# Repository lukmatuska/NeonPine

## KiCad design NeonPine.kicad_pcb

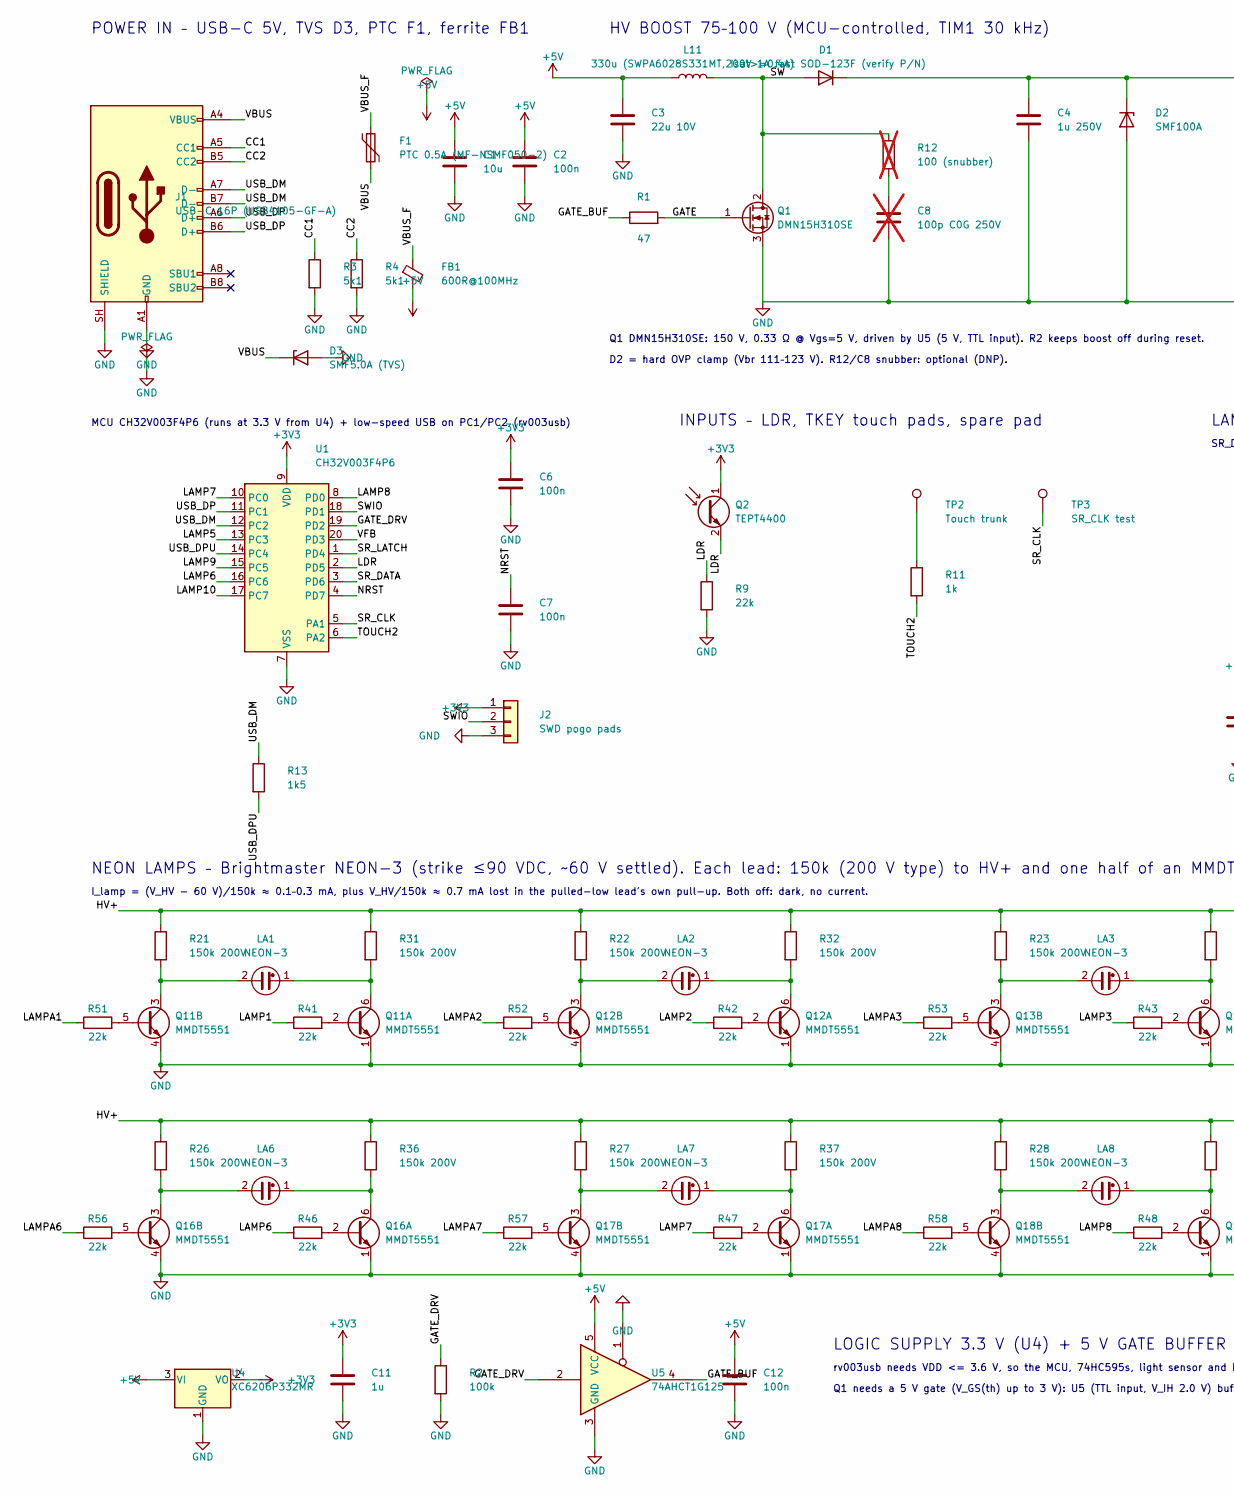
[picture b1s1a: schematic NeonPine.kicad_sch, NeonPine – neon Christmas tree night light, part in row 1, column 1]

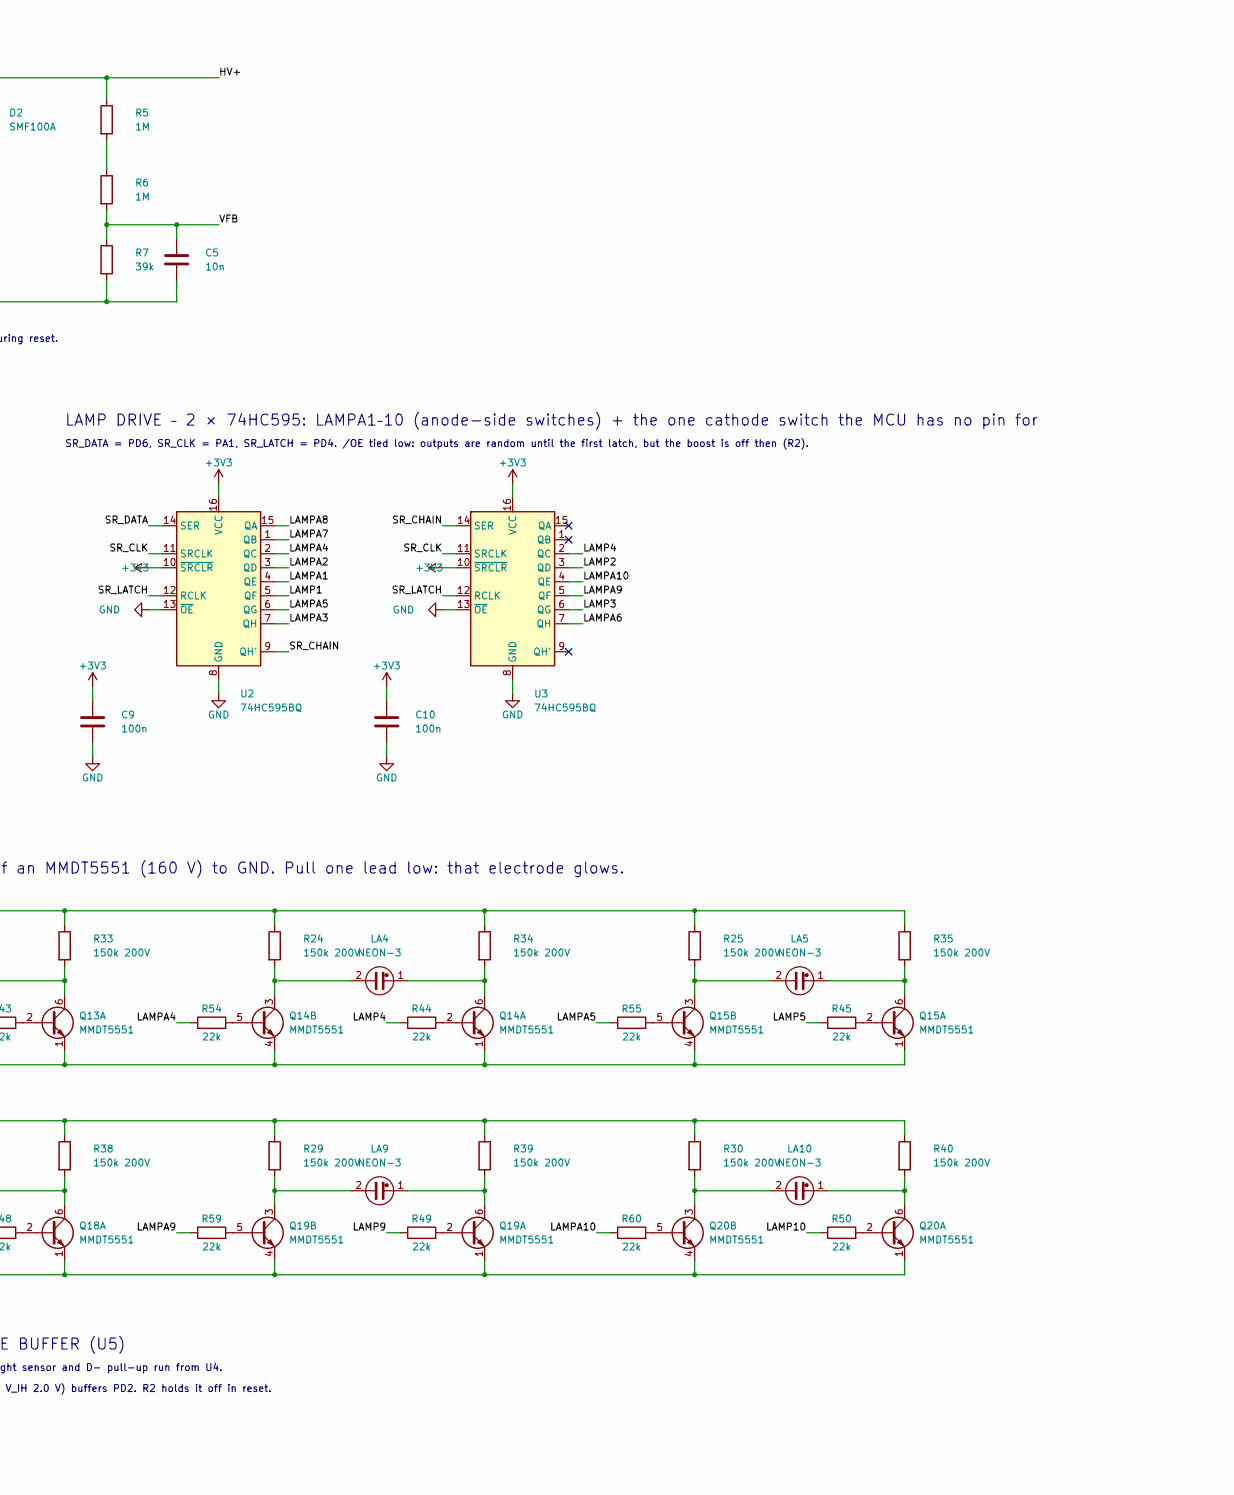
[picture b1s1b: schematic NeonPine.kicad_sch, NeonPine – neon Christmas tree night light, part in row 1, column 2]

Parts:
C1: 10u; C_0603_1608Metric
C2, C6, C7, C9, C10, C12: 100n; C_0402_1005Metric
C3: 22u 10V; C_0805_2012Metric
C4: 1u 250V; C_1210_3225Metric
C5: 10n; C_0402_1005Metric
C8: 100p C0G 250V; C_0805_2012Metric; not fitted
C11: 1u; C_0402_1005Metric
D1: 200V 1A fast SOD-123F (verify P/N); D_SOD-123F
D2: SMF100A; D_SOD-123F
D3: SMF5.0A (TVS); D_SOD-123F
F1: PTC 0.5A (MF-NSMF050-2); Fuse_1206_3216Metric
FB1: 600R@100MHz; L_0603_1608Metric
J1: USB-C 16P (USB4105-GF-A); USB_C_Receptacle_GCT_USB4105-xx-A_16P_TopMnt_Horizontal
J2: SWD pogo pads; Pogo_1x03_P2.54mm
L11: 330u (SWPA6028S331MT, Isat>=0.4A); L_6.3x6.3_H3
LA1, LA2, LA3, LA4, LA5, LA6, LA7, LA8, LA9, LA10: NEON-3; Lamp_Neon_Brightmaster_NEON-3_D4x10_P3.0
Q1: DMN15H310SE; SOT-223-3_TabPin2
Q2: TEPT4400; LED_D3.0mm
Q11, Q12, Q13, Q14, Q15, Q16, Q17, Q18, Q19, Q20: MMDT5551; SOT-363_SC-70-6
R1: 47; R_0402_1005Metric
R2: 100k; R_0402_1005Metric
R3, R4: 5k1; R_0402_1005Metric
R5, R6: 1M; R_0603_1608Metric
R7: 39k; R_0402_1005Metric
R9, R41, R42, R43, R44, R45, R46, R47, R48, R49, R50, R51, R52, R53, R54, R55, R56, R57, R58, R59, R60: 22k; R_0402_1005Metric
R11: 1k; R_0402_1005Metric
R12: 100 (snubber); R_0805_2012Metric; not fitted
R13: 1k5; R_0402_1005Metric
R21, R22, R23, R24, R25, R26, R27, R28, R29, R30, R31, R32, R33, R34, R35, R36, R37, R38, R39, R40: 150k 200V; R_0603_1608Metric
TP2: Touch trunk; TouchPad_D4.0mm_Masked
TP3: SR_CLK test; TestPoint_Pad_1.5x1.5mm
U1: CH32V003F4P6; TSSOP-20_4.4x6.5mm_P0.65mm
U2, U3: 74HC595BQ; DHVQFN-16-1EP_2.5x3.5mm_P0.5mm_EP1x2mm_EPGND
U4: XC6206P332MR; SOT-23
U5: 74AHCT1G125; SOT-353_SC-70-5

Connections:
+3V3: C6.1, C9.1, C10.1, C11.1, J2.1, Q2.1 (C), U1.9 (VDD), U2.10 (~SRCLR), U2.16 (VCC), U3.10 (~SRCLR), U3.16 (VCC), U4.2 (VO)
+5V: C1.1, C2.1, C3.1, C12.1, FB1.2, L11.1, U4.3 (VI), U5.5 (VCC)
/CC1: J1.A5 (CC1), R3.1
/CC2: J1.B5 (CC2), R4.1
/GATE: Q1.1 (G), R1.2
/GATE_BUF: R1.1, U5.4
/GATE_DRV: R2.1, U1.19 (PD2), U5.2
/HV+: C4.1, D1.1 (K), D2.1 (K), R5.1, R21.1, R22.1, R23.1, R24.1, R25.1, R26.1, R27.1, R28.1, R29.1, R30.1, R31.1, R32.1, R33.1, R34.1, R35.1, R36.1, R37.1, R38.1, R39.1, R40.1
/LAMP1: R41.1, U2.5 (QF)
/LAMP2: R42.1, U3.3 (QD)
/LAMP3: R43.1, U3.6 (QG)
/LAMP4: R44.1, U3.2 (QC)
/LAMP5: R45.1, U1.13 (PC3)
/LAMP6: R46.1, U1.16 (PC6)
/LAMP7: R47.1, U1.10 (PC0)
/LAMP8: R48.1, U1.8 (PD0)
/LAMP9: R49.1, U1.15 (PC5)
/LAMP10: R50.1, U1.17 (PC7)
/LAMPA1: R51.1, U2.4 (QE)
/LAMPA2: R52.1, U2.3 (QD)
/LAMPA3: R53.1, U2.7 (QH)
/LAMPA4: R54.1, U2.2 (QC)
/LAMPA5: R55.1, U2.6 (QG)
/LAMPA6: R56.1, U3.7 (QH)
/LAMPA7: R57.1, U2.1 (QB)
/LAMPA8: R58.1, U2.15 (QA)
/LAMPA9: R59.1, U3.5 (QF)
/LAMPA10: R60.1, U3.4 (QE)
/LDR: Q2.2 (E), R9.1, U1.2 (PD5)
/NRST: C7.1, U1.4 (PD7)
/SR_CHAIN: U2.9 (QH'), U3.14 (SER)
/SR_CLK: TP3.1 (1_1), U1.5 (PA1), U2.11 (SRCLK), U3.11 (SRCLK)
/SR_DATA: U1.3 (PD6), U2.14 (SER)
/SR_LATCH: U1.1 (PD4), U2.12 (RCLK), U3.12 (RCLK)
/SW: D1.2 (A), L11.2, Q1.2 (D), R12.1
/SWIO: J2.2, U1.18 (PD1)
/TOUCH2: R11.2, U1.6 (PA2)
/USB_DM: J1.A7 (D-), J1.B7 (D-), R13.1, U1.12 (PC2)
/USB_DP: J1.A6 (D+), J1.B6 (D+), U1.11 (PC1)
/USB_DPU: R13.2, U1.14 (PC4)
/VBUS: D3.1 (K), F1.2, J1.A4 (VBUS), J1.A9 (VBUS), J1.B4 (VBUS), J1.B9 (VBUS)
/VBUS_F: F1.1, FB1.1
/VFB: C5.1, R6.2, R7.1, U1.20 (PD3)
GND: C1.2, C2.2, C3.2, C4.2, C5.2, C6.2, C7.2, C8.2, C9.2, C10.2, C11.2, C12.2, D2.2 (A), D3.2 (A), J1.A1 (GND), J1.A12 (GND), J1.B1 (GND), J1.B12 (GND), J1.SH (SHIELD), J2.3, Q1.3 (S), Q11.1 (E1), Q11.4 (E2), Q12.1 (E1), Q12.4 (E2), Q13.1 (E1), Q13.4 (E2), Q14.1 (E1), Q14.4 (E2), Q15.1 (E1), Q15.4 (E2), Q16.1 (E1), Q16.4 (E2), Q17.1 (E1), Q17.4 (E2), Q18.1 (E1), Q18.4 (E2), Q19.1 (E1), Q19.4 (E2), Q20.1 (E1), Q20.4 (E2), R2.2, R3.2, R4.2, R7.2, R9.2, U1.7 (VSS), U2.8 (GND), U2.13 (~OE), U3.8 (GND), U3.13 (~OE), U4.1 (GND), U5.1, U5.3 (GND)
unnamed: C8.1, R12.2
unnamed: Q11.2 (B1), R41.2
unnamed: LA1.1, Q11.6 (C1), R31.2
unnamed: Q11.5 (B2), R51.2
unnamed: LA1.2, Q11.3 (C2), R21.2
unnamed: Q12.2 (B1), R42.2
unnamed: LA2.1, Q12.6 (C1), R32.2
unnamed: Q12.5 (B2), R52.2
unnamed: LA2.2, Q12.3 (C2), R22.2
unnamed: Q13.2 (B1), R43.2
unnamed: LA3.1, Q13.6 (C1), R33.2
unnamed: Q13.5 (B2), R53.2
unnamed: LA3.2, Q13.3 (C2), R23.2
unnamed: Q14.2 (B1), R44.2
unnamed: LA4.1, Q14.6 (C1), R34.2
unnamed: Q14.5 (B2), R54.2
unnamed: LA4.2, Q14.3 (C2), R24.2
unnamed: Q15.2 (B1), R45.2
unnamed: LA5.1, Q15.6 (C1), R35.2
unnamed: Q15.5 (B2), R55.2
unnamed: LA5.2, Q15.3 (C2), R25.2
unnamed: Q16.2 (B1), R46.2
unnamed: LA6.1, Q16.6 (C1), R36.2
unnamed: Q16.5 (B2), R56.2
unnamed: LA6.2, Q16.3 (C2), R26.2
unnamed: Q17.2 (B1), R47.2
unnamed: LA7.1, Q17.6 (C1), R37.2
unnamed: Q17.5 (B2), R57.2
unnamed: LA7.2, Q17.3 (C2), R27.2
unnamed: Q18.2 (B1), R48.2
unnamed: LA8.1, Q18.6 (C1), R38.2
unnamed: Q18.5 (B2), R58.2
unnamed: LA8.2, Q18.3 (C2), R28.2
unnamed: Q19.2 (B1), R49.2
unnamed: LA9.1, Q19.6 (C1), R39.2
unnamed: Q19.5 (B2), R59.2
unnamed: LA9.2, Q19.3 (C2), R29.2
unnamed: Q20.2 (B1), R50.2
unnamed: LA10.1, Q20.6 (C1), R40.2
unnamed: Q20.5 (B2), R60.2
unnamed: LA10.2, Q20.3 (C2), R30.2
unnamed: R5.2, R6.1
unnamed: R11.1, TP2.1 (1_1)

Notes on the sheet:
POWER IN – USB-C 5V, TVS D3, PTC F1, ferrite FB1
HV BOOST 75–100 V (MCU-controlled, TIM1 30 kHz)
MCU CH32V003F4P6 (runs at 3.3 V from U4) + low-speed USB on PC1/PC2 (rv003usb)
INPUTS – LDR, TKEY touch pads, spare pad
NEON LAMPS – Brightmaster NEON-3 (strike ≤90 VDC, ~60 V settled). Each lead: 150k (200 V type) to HV+ and one half of an MMDT5551 (160 V) to GND. Pull one lead low: that electrode glows.
I_lamp = (V_HV - 60 V)/150k ≈ 0.1–0.3 mA, plus V_HV/150k ≈ 0.7 mA lost in the pulled-low lead's own pull-up. Both off: dark, no current.
LAMP DRIVE – 2 × 74HC595: LAMPA1–10 (anode-side switches) + the one cathode switch the MCU has no pin for
SR_DATA = PD6, SR_CLK = PA1, SR_LATCH = PD4. /OE tied low: outputs are random until the first latch, but the boost is off then (R2).
Q1 DMN15H310SE: 150 V, 0.33 Ω @ Vgs=5 V, driven by U5 (5 V, TTL input). R2 keeps boost off during reset.
D2 = hard OVP clamp (Vbr 111–123 V). R12/C8 snubber: optional (DNP).
LOGIC SUPPLY 3.3 V (U4) + 5 V GATE BUFFER (U5)
rv003usb needs VDD <= 3.6 V, so the MCU, 74HC595s, light sensor and D- pull-up run from U4.
Q1 needs a 5 V gate (V_GS(th) up to 3 V): U5 (TTL input, V_IH 2.0 V) buffers PD2. R2 holds it off in reset.

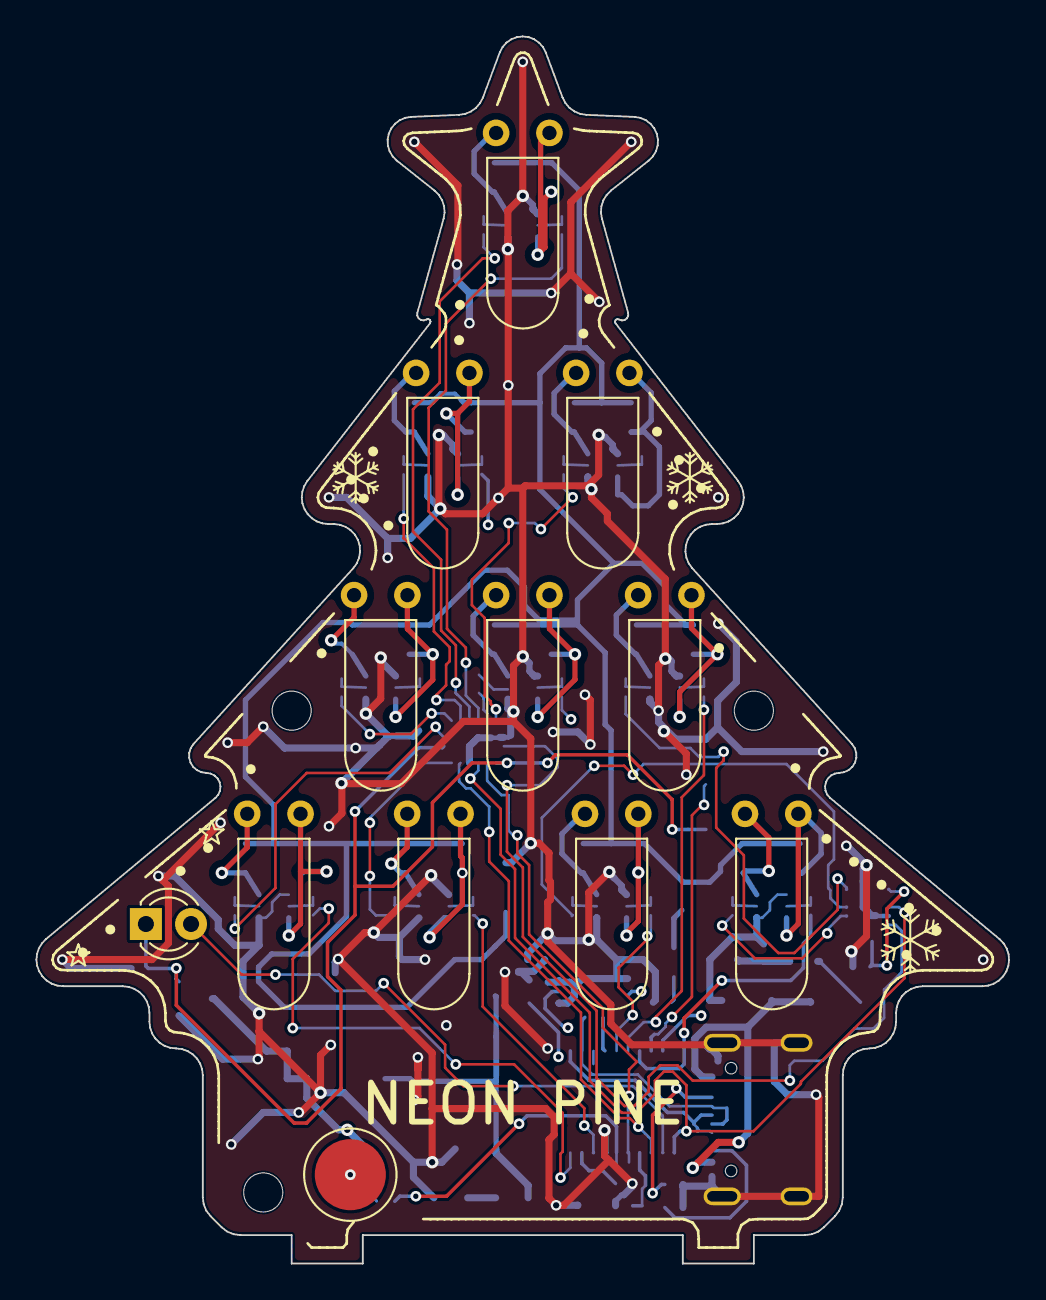
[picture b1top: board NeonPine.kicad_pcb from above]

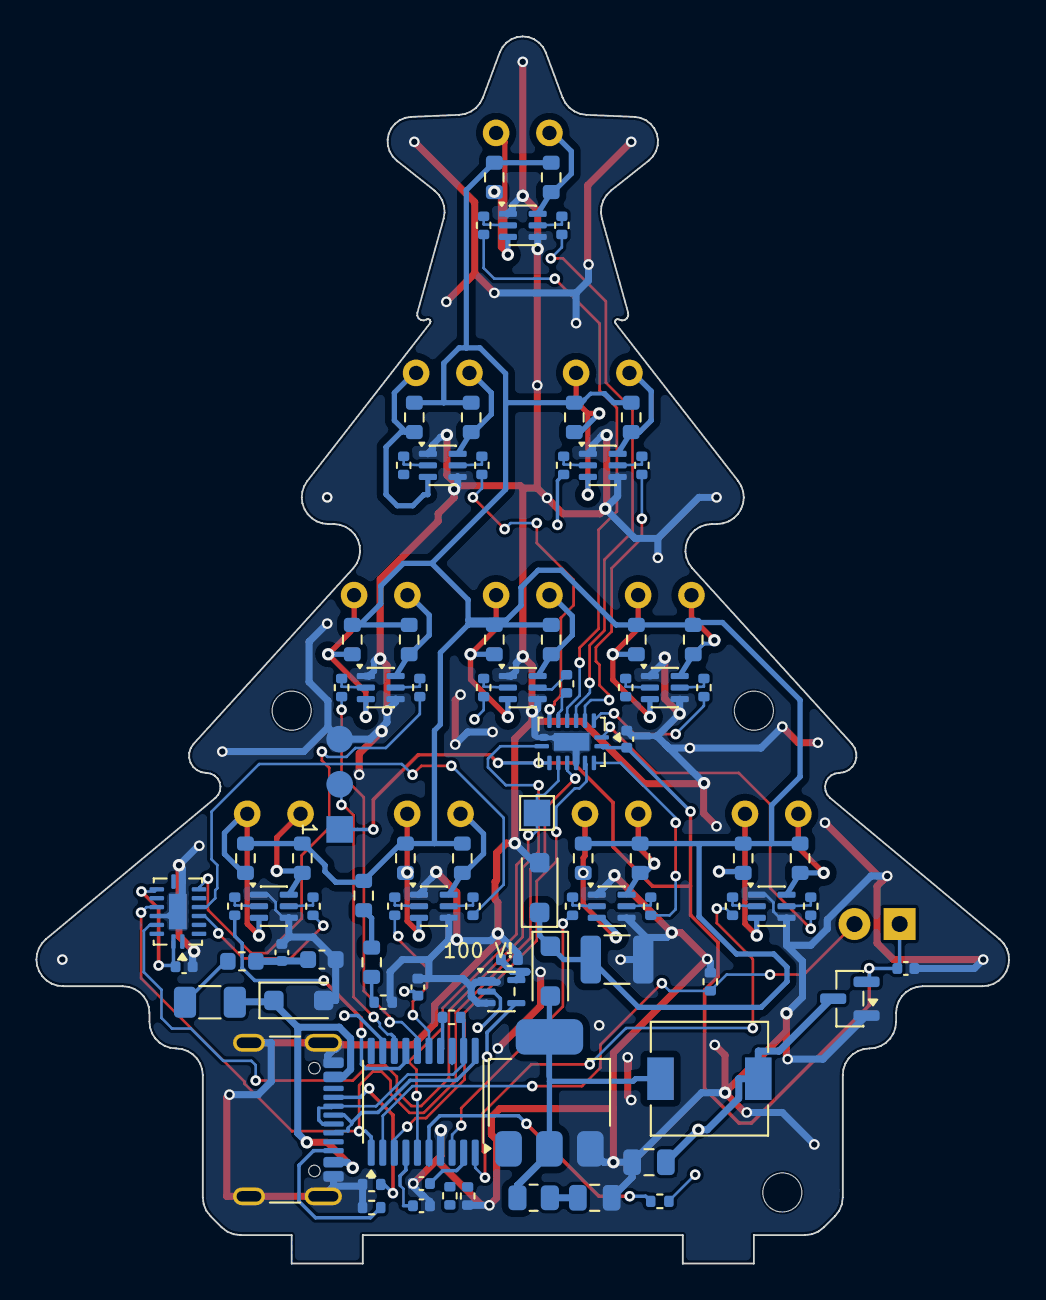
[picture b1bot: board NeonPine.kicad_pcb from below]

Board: 2 copper layers, 54.7 x 69.0 mm, 103 parts (88 on the bottom side), 87 nets.

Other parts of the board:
H1, H2, H3: M2 cover standoff; MountingHole_2.2mm_M2

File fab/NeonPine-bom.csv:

"Comment","Designator","Footprint","Quantity","MPN","LCSC Part #","Description"
"10uF","C1","C_0603_1608Metric","1","","","MLCC X5R/X7R, 10 V or more"
"100nF","C2,C6,C7,C9,C10","C_0402_1005Metric","5","","","MLCC X7R, 16 V or more"
"22uF 10V","C3","C_0805_2012Metric","1","","","MLCC X5R/X7R"
"1uF 250V","C4","C_1210_3225Metric","1","","","MLCC X7R, HV rail bulk cap"
"10nF","C5","C_0402_1005Metric","1","","","MLCC X7R, ADC filter"
"200V 1A fast recovery","D1","D_SOD-123F","1","","","Boost rectifier, SOD-123F; part number not chosen yet"
"SMF100A","D2","D_SOD-123F","1","SMF100A","","TVS 100 V, HV rail clamp"
"SMF5.0A","D3","D_SOD-123F","1","SMF5.0A","","TVS 5 V, USB VBUS"
"MF-NSMF050-2","F1","Fuse_1206_3216Metric","1","MF-NSMF050-2","","PTC resettable fuse 0.5 A hold"
"600Ω@100MHz","FB1","L_0603_1608Metric","1","","","Ferrite bead"
"USB4125-GF-A","J1","USB_C_Receptacle_GCT_USB4125-xx-x_6P_TopMnt_Horizontal","1","USB4125-GF-A","","USB-C power-only receptacle, 6 pin"
"330uH","L11","L_6.3x6.3_H3","1","SWPA6028S331MT","","Shielded power inductor 6x6 mm, Isat >= 0.4 A"
"NEON-3","LA1,LA2,LA3,LA4,LA5,LA6,LA7,LA8,LA9,LA10","Lamp_Neon_Brightmaster_NEON-3_D4x10_P3.0","10","NEON-3","","Brightmaster neon lamp (TME, not stocked at LCSC); hand-soldered"
"DMN15H310SE","Q1","SOT-223-3_TabPin2","1","DMN15H310SE","",""
"TEPT4400","Q2","LED_D3.0mm","1","TEPT4400","","Ambient light phototransistor, THT"
"MMDT5551","Q11,Q12,Q13,Q14,Q15,Q16,Q17,Q18,Q19,Q20","SOT-363_SC-70-6","10","MMDT5551(RANGE:100-300)","C148105","Dual NPN 160 V, JSCJ (pin-compatible with Diodes MMDT5551)"
"47Ω","R1","R_0402_1005Metric","1","","",""
"100kΩ","R2","R_0402_1005Metric","1","","",""
"5.1kΩ","R3,R4","R_0402_1005Metric","2","","",""
"1MΩ","R5,R6","R_0603_1608Metric","2","","",""
"39kΩ","R7","R_0402_1005Metric","1","","",""
"22kΩ","R9,R41,R42,R43,R44,R45,R46,R47,R48,R49,R50,R51,R52,R53,R54,R55,R56,R57,R58,R59,R60","R_0402_1005Metric","21","","",""
"1kΩ","R11","R_0402_1005Metric","1","","",""
"33Ω","R13","R_0402_1005Metric","1","","","SPI clock series resistor"
"150kΩ 200V","R21,R22,R23,R24,R25,R26,R27,R28,R29,R30,R31,R32,R33,R34,R35,R36,R37,R38,R39,R40","R_0603_1608Metric","20","","","Thick film, >= 200 V working voltage (e.g. RCV0603)"
"CH32V003F4P6","U1","TSSOP-20_4.4x6.5mm_P0.65mm","1","CH32V003F4P6","",""
"74HC595BQ","U2,U3","DHVQFN-16-1EP_2.5x3.5mm_P0.5mm_EP1x2mm_EPGND","2","74HC595BQ,115","",""

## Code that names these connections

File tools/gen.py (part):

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P('C3','Device','C',121.92,48.26,'22u 10V','Capacitor_SMD:C_0805_2012Metric',{'1':'+5V','2':'GND'})
P('L11','Device','L',134.62,40.64,'330u (SWPA6028S331MT, Isat>=0.4A)','NeonPine:L_6.3x6.3_H3',{'1':'+5V','2':'SW'})
P('D1','Device','D',152.4,33.02,'200V 1A fast SOD-123F (verify P/N)','Diode_SMD:D_SOD-123F',{'2':'SW','1':'HV+'})
P('Q1','Transistor_FET','Q_NMOS_GDS',144.78,58.42,'DMN15H310SE','Package_TO_SOT_SMD:SOT-223-3_TabPin2',{'1':'GATE','2':'SW','3':'GND'})
# Q1's V_GS(th) is up to 3 V, so the 3.3 V MCU drives the gate through a 5 V buffer with TTL input thresholds (V_IH 2.0 V).
# R2 holds the buffer input (and so the gate) low during reset and programming.
P('U5','74xGxx','74AHCT1G125',121.92,269.24,'74AHCT1G125','Package_TO_SOT_SMD:SOT-353_SC-70-5',{'1':'GND','2':'GATE_DRV','3':'GND','4':'GATE_BUF','5':'+5V'})
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P('R6','Device','R',208.28,53.34,'1M',R06,{'1':'FB_MID','2':'VFB'})
P('R7','Device','R',208.28,66.04,'39k',R04,{'1':'VFB','2':'GND'})
P('C5','Device','C',218.44,66.04,'10n',C04,{'1':'VFB','2':'GND'})
# --- MCU. Lamp -> pin map (PC0, PC3, PC5-7 = pins 10, 13, 15-17, PD0 = 8) comes from tools/pinswap.py when present
_lp=os.path.join(os.path.dirname(os.path.abspath(__file__)),'lamp_pins.json')
import json
_j=json.load(open(_lp)) if os.path.exists(_lp) else {}
SR_SLOTS=_j.get('sr')                       # AC branch format: {"mcu": {pin: LAMPn}, "sr": [16 shift-register slots]}
LAMP_PINS=_j['mcu'] if 'mcu' in _j else _j if _j else {'10':'LAMP1','11':'LAMP2','12':'LAMP3','13':'LAMP4','14':'LAMP5',
  '15':'LAMP6','16':'LAMP7','17':'LAMP8','8':'LAMP9','1':'LAMP10'}
# --- MCU
LAMP_PINS={k:v for k,v in LAMP_PINS.items() if k not in ('1','3','5','11','12','14')}   # PD4/PD6/PA1: shift registers, PC1/PC2/PC4: USB
P('U1','MCU_WCH_RiscV','CH32V003FxPx',60.96,121.92,'CH32V003F4P6','Package_SO:TSSOP-20_4.4x6.5mm_P0.65mm',
  {**LAMP_PINS, '18':'SWIO','19':'GATE_DRV','20':'VFB','2':'LDR','4':'NRST',
   '5':'SR_CLK','6':'TOUCH2','3':'SR_DATA','1':'SR_LATCH','9':'+3V3','7':'GND',
   '11':'USB_DP','12':'USB_DM','14':'USB_DPU'})   # rv003usb usb_config.h: USB_PORT C, DP 1, DM 2, DPU 4
P('C6','Device','C',101.6,106.68,'100n',C04,{'1':'+3V3','2':'GND'})
# USB: 1.5k D- pull-up switched by PC4 (low-speed attach / detach). rv003usb's optional 33R series resistors are left out
# (no room in the pot); PC4 lets firmware re-enumerate without pulsing D- directly.
P('R13','Device','R',55.88,160.02,'1k5',R04,{'1':'USB_DM','2':'USB_DPU'})
P('C7','Device','C',101.6,129.54,'100n',C04,{'1':'NRST','2':'GND'})
P('J2','Connector_Generic','Conn_01x03',101.6,149.86,'SWD pogo pads','NeonPine:Pogo_1x03_P2.54mm',
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P('C10','Device','C',287.02,149.86,'100n',C04,{'1':'+3V3','2':'GND'})

notes=[(25.4,25.4,'POWER IN – USB-C 5V, TVS D3, PTC F1, ferrite FB1'),(119.38,25.4,'HV BOOST 75–100 V (MCU-controlled, TIM1 30 kHz)'),
 (25.4,96.52,'MCU CH32V003F4P6 (runs at 3.3 V from U4) + low-speed USB on PC1/PC2 (rv003usb)'),(132.08,96.52,'INPUTS – LDR, TKEY touch pads, spare pad'),
 (25.4,177.8,'NEON LAMPS – Brightmaster NEON-3 (strike ≤90 VDC, ~60 V settled). Each lead: 150k (200 V type) to HV+ and one half of an MMDT5551 (160 V) to GND. Pull one lead low: that electrode glows.'),
 (25.4,181.61,'I_lamp = (V_HV - 60 V)/150k ≈ 0.1–0.3 mA, plus V_HV/150k ≈ 0.7 mA lost in the pulled-low lead\'s own pull-up. Both off: dark, no current.'),
 (228.6,96.52,'LAMP DRIVE – 2 × 74HC595: LAMPA1–10 (anode-side switches) + the one cathode switch the MCU has no pin for'),
 (228.6,100.33,'SR_DATA = PD6, SR_CLK = PA1, SR_LATCH = PD4. /OE tied low: outputs are random until the first latch, but the boost is off then (R2).'),
 (119.38,81.28,'Q1 DMN15H310SE: 150 V, 0.33 Ω @ Vgs=5 V, driven by U5 (5 V, TTL input). R2 keeps boost off during reset.'),
 (119.38,85.09,'D2 = hard OVP clamp (Vbr 111–123 V). R12/C8 snubber: optional (DNP).'),
 (160.02,264.16,'LOGIC SUPPLY 3.3 V (U4) + 5 V GATE BUFFER (U5)'),
 (160.02,267.97,'rv003usb needs VDD <= 3.6 V, so the MCU, 74HC595s, light sensor and D- pull-up run from U4.'),
 (160.02,271.78,'Q1 needs a 5 V gate (V_GS(th) up to 3 V): U5 (TTL input, V_IH 2.0 V) buffers PD2. R2 holds it off in reset.')]

for ref,lib,name,*_ ,fp,nets,dnp,unit in parts:
    if fp and not ref.startswith('#'):
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
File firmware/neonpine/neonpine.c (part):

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// Pin map and lamp tables: docs/mcu-netlist.md, hardware: DESIGN.md §2, animations: anim.c (a port of
// the NeonPine simulator artifact).
//
// * HV boost: PD6 = TIM2_CH3 (full remap), 40 kHz, fixed 20 us gate pulses (I_pk 0.30 A). Pulse skipping
//   against the PD3 (A4) feedback: every main-loop pass reads HV and lets the next pulse through or not.
//   Soft start 0.2 V/ms.
// * Protection (firmware only; the hardware limits are R2, D2, F1): overvoltage trip, "no rise" trip
//   (HV below 20 V for 1 s while boosting: open feedback, dead boost, shorted rail), IWDG.
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//   and HV stays at 100 V. Rail dimming is selectable (npctl.py dim rail) to try.
// * TP2 touch (DESIGN.md §2.4): tap = next animation, double tap = sleep timer (dims over 20 min, then
//   off), triple tap = style, hold = brightness ramp, hold 3 s = off / on.
// * Light sensor (TEPT4400 on PA1): read in a 0.5 ms all-dark slot every 100 ms, so the tree's own light
//   doesn't count. Off in daylight, on at dusk, room-adaptive brightness, wave a hand = next animation.
// * USB HID 1209:D003 with feature reports: 0xAA status, 0xAB commands (../tools/npctl.py), 0xAC live
//   frames and 0xAE store pages (../../companion). minichlink reboots it into the rv003usb bootloader
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#define BOOST_PERIOD      1200     // TIM2 ticks at 48 MHz -> 40 kHz (default, npctl.py freq changes it)
#define PERIOD_MAX        9600     // 5 kHz
#define PERIOD_MARGIN     192      // >= 4 us off-time per period: L11 must empty (DCM) before the next pulse
#define TON_DEFAULT       960      // gate on-time, ticks: 20 us -> I_pk 0.30 A (L11 CR5040-331M: 400 mA)
                                   // 20 us / 40 kHz measured best: ~0.45 W, all lamps at full -> 75 V
#define TON_MIN           48       // 1 us
#define TON_LIMIT         960      // 20 us = the 60 % duty clamp of DESIGN.md §2.2 (I_pk 0.30 A)
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enum { FAULT_NONE = 0, FAULT_OVERVOLTAGE = 1, FAULT_NO_RISE = 2 };

// ---- GPIO --------------------------------------------------------------------------------------
#define SR_DATA_D   (1u << 7)  // PD7 (NRST pin -> option bytes must set RST_MODE = GPIO)
#define SR_LATCH_D  (1u << 5)  // PD5
#define SR_CLK_C    (1u << 7)  // PC7 (also TP3)

#define ADC_CH_TOUCH 0  // PA2, TP2 through R11
#define ADC_CH_LDR   1  // PA1, TEPT4400 emitter, 22k to GND
#define ADC_CH_VFB   4  // PD3, HV divider
#define ADC_CH_VREF  8  // internal 1.2 V reference

// ---- Lamps -------------------------------------------------------------------------------------
// The lamp switches are collected in one 32-bit output word:
// bits 0-15 = 74HC595 chain word (U3 QH = bit 15 ... U2 QA = bit 0), bits 16-22 = PC0-PC6, bit 24 = PD0.
#define SW_SR(b) (b)
#define SW_PC(b) (16 + (b))
#define SW_PD(b) (24 + (b))
#define OUT_PC_MASK 0x7f  // PC7 is SR_CLK, not a lamp switch
#define OUT_PD_MASK 0x01

// {K side = lamp pad 1 (net LAMPn), A side = lamp pad 2 (net LAMPAn)} – docs/mcu-netlist.md "Lamps".
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	CMD_HV = 2,           // [2] = volts (0 = boost off)
	CMD_LAMPS = 3,        // [2..5] = lamp word (LE), switches to manual mode
	CMD_CLEAR_FAULT = 4,
	CMD_TON = 5,          // [2..3] = gate on-time in 48 MHz ticks (LE)
	CMD_PAUSE = 6,        // [2] = 0 run / 1 pause (test show)
	CMD_TOUCH_DELTA = 7,  // [2..3] = touch threshold above baseline (0 = default)
	CMD_PERIOD = 8,       // [2..3] = boost period in 48 MHz ticks (LE)
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static void boost_init( void )
{
	RCC->APB1PCENR |= RCC_APB1Periph_TIM2;
	AFIO->PCFR1 = ( AFIO->PCFR1 & ~AFIO_PCFR1_TIM2_REMAP ) | AFIO_PCFR1_TIM2_REMAP_FULLREMAP;  // CH3 -> PD6

	TIM2->PSC = 0;
	TIM2->ATRLR = BOOST_PERIOD - 1;
	TIM2->CH3CVR = 0;                                            // gate low
	TIM2->CHCTLR2 = TIM_OC3M_2 | TIM_OC3M_1 | TIM_OC3PE;         // PWM mode 1, preloaded
	TIM2->CCER = TIM_CC3E;                                       // only CH3: CH1/CH2/CH4 (PC1/PC7/PD5) stay GPIO
	TIM2->CTLR1 = TIM_ARPE;
	TIM2->SWEVGR = TIM_UG;
	TIM2->CTLR1 |= TIM_CEN;

	funPinMode( PD6, GPIO_CFGLR_OUT_10Mhz_AF_PP );
}

static void set_fault( int f )
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{
	funGpioInitAll();

	// Lamp switches PC0-PC6 + PD0, 595 interface PC7 / PD5 / PD7: outputs, all low.
	GPIOC->BSHR = 0xffu << 16;
	GPIOD->BSHR = ( SR_DATA_D | SR_LATCH_D | 1u ) << 16;
	GPIOC->CFGLR = 0x11111111 * GPIO_CFGLR_OUT_50Mhz_PP;  // all of port C
	funPinMode( PD0, GPIO_CFGLR_OUT_10Mhz_PP );
	funPinMode( PD5, GPIO_CFGLR_OUT_50Mhz_PP );
	funPinMode( PD7, GPIO_CFGLR_OUT_50Mhz_PP );

	// Every lamp switch off (also latches the random power-up state of the 595s away).
	outs_write( 0, 0xffffffff );
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	}

	// Analog inputs
	funPinMode( PD3, GPIO_CFGLR_IN_ANALOG );
	funPinMode( PA1, GPIO_CFGLR_IN_ANALOG );
}

static void iwdg_init( void )
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	SystemInit();
	stack_paint();

	gpio_init();  // lamps off before anything else (R2 holds the boost gate low until TIM2 runs)

	// Settings and custom animations from the store
	anim_store_changed();
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	status.uid = *(volatile uint32_t *)0x1ffff7e8 ^ *(volatile uint32_t *)0x1ffff7ec ^ *(volatile uint32_t *)0x1ffff7f0;

	// Force re-enumeration: the bootloader may have just been on the bus with the same D- pull-up.
	funPinMode( PD4, GPIO_CFGLR_OUT_10Mhz_PP );
	GPIOD->BSHR = 1u << ( 4 + 16 );
	Delay_Ms( 20 );
	usb_setup();
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
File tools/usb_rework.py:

#!/usr/bin/env python3
"""One-off board update for the USB rework (branch USB). Applies the new netlist to the *existing* board without touching
the rest of the routing:
  * J1: USB4125 (power-only, 6P) -> USB4105-GF-A (USB 2.0, 16P, same GCT family and shell pattern), PCB-edge line kept at x 118.
  * C7 (NRST cap) removed: PD7 is SR_DATA now.
  * new parts R13/R14 (68R series), D4/D5 (3.6 V zeners, SOD-882), R15 (1k5 D- pull-up); R3/R4 (CC) moved to the strip below J1.
  * every pad gets its net (and every footprint its symbol path) from the netlist.
  * rip-up: only the copper of the nets whose MCU pin moved, inside the U1 / J1 window (SR_*, LDR, GATE_DRV, CC, VBUS/GND at
    J1), the old LAMP10 route and NRST. LAMP10 / LAMPA10 at U3 are re-drawn here (U3 QE / QD).
The open connections are then routed by tools/route_local.py (Freerouting with every other track locked).
Usage: kicad-cli sch export netlist --format kicadsexpr -o np.net NeonPine.kicad_sch
       python3 tools/usb_rework.py np.net"""
import os, sys
import pcbnew
HERE = os.path.dirname(os.path.abspath(__file__)); sys.path.insert(0, HERE)
from sx import parse

PCB = os.path.join(HERE, '..', 'NeonPine.kicad_pcb')
FP = '/usr/share/kicad/footprints/'
MM = pcbnew.FromMM
seq = lambda c: [c[i] for i in range(len(c))]
V = lambda x, y: pcbnew.VECTOR2I(MM(x), MM(y))
mm = pcbnew.ToMM

# ---- netlist
t = parse(open(sys.argv[1]).read())[0]
g = lambda e, k: [x for x in e if isinstance(x, list) and x[0] == k]
comps = {}
for c in g(t, 'components')[0][1:]:
    ref = g(c, 'ref')[0][1].strip('"')
    comps[ref] = dict(value=g(c, 'value')[0][1].strip('"'), fp=g(c, 'footprint')[0][1].strip('"'),
                      uuid=g(c, 'tstamps')[0][1].strip('"'))
pinnet = {}
for n in g(t, 'nets')[0][1:]:
    name = g(n, 'name')[0][1].strip('"')
    for nd in g(n, 'node'):
        pinnet[(g(nd, 'ref')[0][1].strip('"'), g(nd, 'pin')[0][1].strip('"'))] = name

b = pcbnew.LoadBoard(PCB)

def load(fpid):
    """pcbnew.FootprintLoad() is broken in this KiCad 10 build (plugin lookup); the S-expression IO class works"""
    lib, name = fpid.split(':')
    f = pcbnew.PCB_IO_KICAD_SEXPR().FootprintLoad(FP + lib + '.pretty', name)
    f.SetFPID(pcbnew.LIB_ID(lib, name))
    return f

# after any BOARD.Remove() this build's SWIG layer hands back untyped objects from every call that returns a FOOTPRINT
# (FootprintLoad, FindFootprintByReference, ...): load / look up everything first and remove items only at the very end
NEW = {ref: load(comps[ref]['fp']) for ref in ('J1', 'R13', 'R14', 'D4', 'D5', 'R15')}
FPS = {f.GetReference(): f for f in seq(b.Footprints())}
OLD = [FPS.pop('C7'), FPS.pop('J1')]

def place(ref, x, y, rot, pad1=None):
    """put footprint ref on B.Cu at (x, y) with orientation rot; pad1 = 'top'/'bottom'/'left'/'right' (board view) flips it 180
    if pad 1 ends up on the wrong side"""
    f = FPS.get(ref)
    if f is None:
        f = FPS[ref] = NEW[ref]; f.SetReference(ref); f.GetField(pcbnew.FIELD_T_DATASHEET).SetText('~'); b.Add(f)
    if not f.IsFlipped():
        f.Flip(f.GetPosition(), pcbnew.FLIP_DIRECTION_LEFT_RIGHT)
    f.SetPosition(V(x, y)); f.SetOrientationDegrees(rot)
    if pad1:
        p = f.FindPadByNumber('1').GetPosition(); c = f.GetPosition()
        ok = {'top': p.y < c.y, 'bottom': p.y > c.y, 'left': p.x < c.x, 'right': p.x > c.x}[pad1]
        if not ok: f.SetOrientationDegrees(rot + 180)
    return f

# ---- footprints
j1 = NEW['J1']
# USB4125 footprint had its PCB-edge line at local y 3.4 (board x 118.0); USB4105 has it at 3.675 -> centre x 114.325
place('J1', 118.0 - 3.675, 103.5, -90)
place('R13', 107.45, 107.65, 90, 'top')      # D+ series, MCU side (pad 1) up
place('R14', 108.45, 107.65, 90, 'top')      # D- series, pad 1 up under U1 pin 1
place('D4', 107.10, 109.25, 0, 'right')      # D+ zener, cathode (pad 1) right
place('D5', 108.75, 109.25, 0, 'right')      # D- zener
place('R4', 110.60, 109.37, 0, 'left')       # CC2 (pad 1) left
place('R15', 112.50, 109.37, 0, 'right')     # VBUS (pad 1) right
place('R3', 114.45, 109.37, 0, 'left')       # CC1

def drag(ref, dx, dy):
    """move a placed footprint and the track ends sitting on its pads"""
    f = FPS[ref]; d = V(dx, dy)
    on = lambda q: any(p.HitTest(q) and p.IsOnLayer(tr.GetLayer()) for p in f.Pads())
    for tr in [x.Cast() for x in seq(b.Tracks())]:
        if tr.GetClass() == 'PCB_VIA': continue
        a0, a1 = on(tr.GetStart()), on(tr.GetEnd())
        if a0: tr.SetStart(tr.GetStart() + d)
        if a1: tr.SetEnd(tr.GetEnd() + d)
    f.SetPosition(f.GetPosition() + d)
drag('C5', 0, -0.16)    # J1's (longer) courtyard reaches y 98.18

for ref, f in FPS.items():
    if ref not in comps: continue
    f.SetValue(comps[ref]['value'])
    f.SetPath(pcbnew.KIID_PATH('/' + comps[ref]['uuid']))
    for p in f.Pads():
        if not p.GetNumber(): continue
        name = pinnet.get((ref, p.GetNumber()))
        if name is None: p.SetNetCode(0); continue
        net = b.FindNet(name)
        if net is None:
            net = pcbnew.NETINFO_ITEM(b, name); b.Add(net)
        p.SetNet(net)
missing = set(comps) - set(FPS)
assert not missing, missing

# ---- rip-up
def inside(p, w): return w[0] <= mm(p.x) <= w[2] and w[1] <= mm(p.y) <= w[3]
W_U1 = (102.5, 99.5, 117.0, 110.5)     # under / around U1, the U1-J1 gap, the strip below
W_J1 = (106.3, 98.5, 118.6, 110.5)     # J1 and the strip below it
W_G = (109.65, 96.7, 118.6, 110.5)
rip = {'/SR_LATCH': W_U1, '/SR_DATA': W_U1, '/SR_CLK': W_U1, '/SR_CHAIN': W_U1, '/LDR': W_U1, '/GATE_DRV': W_U1,
       '/VBUS': W_J1, 'GND': W_J1}
gone = {'/NRST', '/LAMP10', '/CC1', '/CC2'}
kill = []
for tr in [x.Cast() for x in seq(b.Tracks())]:
    net = tr.GetNetname()
    if net in gone: kill.append(tr); continue
    if net == '/LAMPA10':    # LAMPA10 leaves U3 one pin lower now (QD); LAMP10 takes QE, straight to R50
        if tr.GetClass() != 'PCB_VIA' and tr.GetLayer() == pcbnew.B_Cu and min(mm(tr.GetStart().x), mm(tr.GetEnd().x)) > 117.0 \
                and mm(tr.GetStart().y) < 93.5: kill.append(tr)
        continue
    if net == 'GND' and tr.GetClass() != 'PCB_VIA' and (inside(tr.GetStart(), W_G) or inside(tr.GetEnd(), W_G)):
        kill.append(tr); continue    # GND stubs to the old J1 shell / around C5 (the pours connect GND)
    if net not in rip: continue
    w = rip[net]
    if tr.GetClass() == 'PCB_VIA':
        if inside(tr.GetPosition(), w): kill.append(tr)
    elif inside(tr.GetStart(), w) and inside(tr.GetEnd(), w):
        kill.append(tr)

def track(net, pts, w=0.15, layer=pcbnew.B_Cu):
    for a, c in zip(pts, pts[1:]):
        s = pcbnew.PCB_TRACK(b); s.SetStart(V(*a)); s.SetEnd(V(*c)); s.SetWidth(MM(w)); s.SetLayer(layer)
        s.SetNet(b.FindNet(net)); b.Add(s)
u3, r50 = FPS['U3'], FPS['R50']
xy = lambda f, pad: (mm(f.FindPadByNumber(pad).GetPosition().x), mm(f.FindPadByNumber(pad).GetPosition().y))
assert u3.FindPadByNumber('4').GetNetname() == '/LAMP10' and u3.FindPadByNumber('3').GetNetname() == '/LAMPA10'
track('/LAMP10', [xy(u3, '4'), xy(r50, '1')])
qd = xy(u3, '3'); track('/LAMPA10', [qd, (117.604, qd[1]), (117.127, 93.027)])
print('J1 pads:', {p.GetNumber(): (round(mm(p.GetPosition().x), 3), round(mm(p.GetPosition().y), 3))
                   for p in j1.Pads() if p.GetNumber() in ('A5', 'B5', 'A6', 'B7')})
for it in kill + OLD: b.Remove(it)
pcbnew.SaveBoard(PCB, b)
print('removed', len(kill), 'track items and', [f.GetReference() for f in OLD])
sys.stdout.flush(); os._exit(0)     # skip interpreter teardown: the GC of removed SWIG objects segfaults in this build
